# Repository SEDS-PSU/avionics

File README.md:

# Avionics

## /electronics
Board files and etc for avionics and teststand electronics

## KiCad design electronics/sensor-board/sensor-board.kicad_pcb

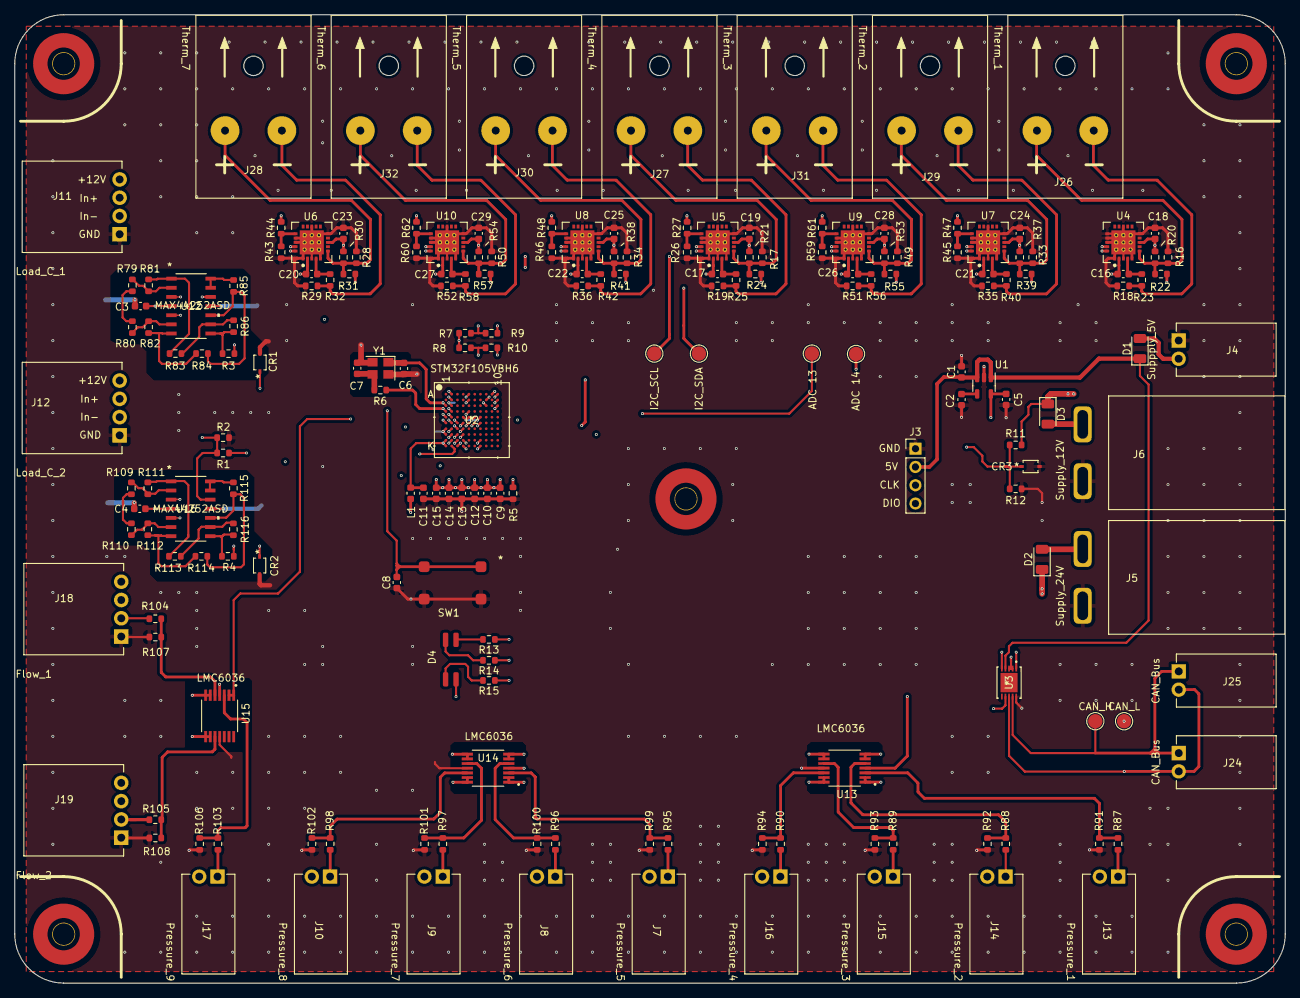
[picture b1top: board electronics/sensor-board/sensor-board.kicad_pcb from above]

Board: 4 copper layers, 176.6 x 134.6 mm, 193 parts (0 on the bottom side), 126 nets.

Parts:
C1, C5: 1uF; C_0603_1608Metric
C2: 10nF; C_0603_1608Metric
C3, C4, C8, C9, C10, C11, C12, C13, C14, C15: 100nF; C_0603_1608Metric
C6, C7: 20pF; C_0603_1608Metric
C16, C17, C18, C19, C20, C21, C22, C23, C24, C25, C26, C27, C28, C29: 0.1uF; C_0603_1608Metric
CR1, CR2, CR3: MM3Z3V6C
D1, D2, D3: D; D_1206_3216Metric
D4: LED_RGBA; RGB LED
J3: SWD Header; PinHeader_1x04_P2.54mm_Vertical
J4: Suppply_5V; SL_2.54_H_2pin
J5: Supply_24V; PowerPoleThroughHole
J6: Supply_12V; PowerPoleThroughHole
J7: Pressure_5; SL_2.54_H_2pin
J8: Pressure_6; SL_2.54_H_2pin
J9: Pressure_7; SL_2.54_H_2pin
J10: Pressure_8; SL_2.54_H_2pin
J11: Load_C_1; SL_2.54_H_4pin
J12: Load_C_2; SL_2.54_H_4pin
J13: Pressure_1; SL_2.54_H_2pin
J14: Pressure_2; SL_2.54_H_2pin
J15: Pressure_3; SL_2.54_H_2pin
J16: Pressure_4; SL_2.54_H_2pin
J17: Pressure_9; SL_2.54_H_2pin
J18: Flow_1; SL_2.54_H_4pin
J19: Flow_2; SL_2.54_H_4pin
J24, J25: CAN_Bus; SL_2.54_H_2pin
J26: Therm_1; K_type_thermo_conn_F
J27: Therm_4; K_type_thermo_conn_F
J28: Therm_7; K_type_thermo_conn_F
J29: Therm_2; K_type_thermo_conn_F
J30: Therm_5; K_type_thermo_conn_F
J31: Therm_3; K_type_thermo_conn_F
J32: Therm_6; K_type_thermo_conn_F
L1: 10uH; L_0603_1608Metric
R1: 3.2k; R_0603_1608Metric
R2, R9, R10, R22, R23, R24, R25, R31, R32, R39, R40, R41, R42, R55, R56, R57, R58, R87, R88, R89, R90, R91, R92, R93, R94, R95, R96, R97, R98, R99, R100, R101, R102, R103, R104, R105, R106, R107, R108: 100; R_0603_1608Metric
R3, R4: 200; R_0603_1608Metric
R5, R26, R43, R45, R46, R59, R60: 10k; R_0603_1608Metric
R6: 0k; R_0603_1608Metric
R7, R8: 4.7k; R_0603_1608Metric
R11: 8.2k; R_0603_1608Metric
R12: 1.8k; R_0603_1608Metric
R13: 261; R_0603_1608Metric
R14, R15: 140; R_0603_1608Metric
R16, R17, R28, R33, R34, R49, R50: 2.49M; R_0603_1608Metric
R18, R19, R29, R35, R36, R51, R52: 487k; R_0603_1608Metric
R20, R21, R30, R37, R38, R53, R54: 2M; R_0603_1608Metric
R27: 7.5k; R_0603_1608Metric
R44: 43k; R_0603_1608Metric
R47: 2.2k; R_0603_1608Metric
R48: 13k; R_0603_1608Metric
R61: 4.3k; R_0603_1608Metric
R62: 22k; R_0603_1608Metric
R79, R109: 1.2k; R_0603_1608Metric
R80, R110: 14.3; R_0603_1608Metric
R81, R82, R83, R84, R85, R86, R111, R112, R113, R114, R115, R116: 50k; R_0603_1608Metric
SW1: SW_Push_Dual; Button CS1102
TP1: ADC 14; TestPoint_Pad_D2.0mm
TP2: TestPoint; seds-logo-2
TP3: TestPoint; seds-logo-back-2
TP6: CAN_H; TestPoint_Pad_D2.0mm
TP7: CAN_L; TestPoint_Pad_D2.0mm
TP8: I2C_SCL; TestPoint_Pad_D2.0mm
TP9: I2C_SDA; TestPoint_Pad_D2.0mm
TP10, TP11, TP12, TP13, TP14: TestPoint; 3mm hole
TP15: ADC 13; TestPoint_Pad_D2.0mm
U1: LD3985M33R_SOT23; SOT-23-5
U2: STM32F105VBH6
U3: MAX33014EATB+; MAX33014EATB&plus_
U4, U5, U6, U7, U8, U9, U10: MCP96RL01T; MCP96RL01T_QFN
U12, U16: MAX44252ASD; MAX44252ASD&plus_
U13, U14, U15: LMC6036; SOP65P640X120-14N
Y1: 36 MHz; Crystal_SMD_3225-4Pin_3.2x2.5mm

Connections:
+3V3: C5.1, C9.1, C10.1, C12.1, C13.1, C14.1, C15.1, C18.1, C19.1, C23.1, C24.1, C25.1, C28.1, C29.1, D4.4 (A), L1.2, R1.2, R7.1, R8.1, R20.1, R21.1, R27.2, R30.1, R37.1, R38.1, R44.2, R47.2, R48.2, R53.1, R54.1, R61.2, R62.2, U1.5 (VOUT), U2.B2 (VBAT), U2.D2 (VDD_5), U2.F4 (VDD_4), U2.F5 (VDD_3), U2.F6 (VDD_2), U2.F7 (VDD_1), U3.7 (VL), U4.8 (VDD), U5.8 (VDD), U6.8 (VDD), U7.8 (VDD), U8.8 (VDD), U9.8 (VDD), U10.8 (VDD), U13.4 (VDD), U14.4 (VDD), U15.4 (VDD)
+5V: C1.1, D1.1 (K), J3.2, U1.1 (VIN), U1.3 (INH), U3.4 (VDD)
+12V: C3.1, C4.1, D3.1 (K), J11.4, J12.4, R11.1, U12.4 (VDD), U16.4 (VDD)
+24V: D2.1 (K), J7.2, J8.2, J9.2, J10.2, J13.2, J14.2, J15.2, J16.2, J17.2, J18.4, J19.4
/ADC12_IN0: CR1.1, R3.2, U2.G2 (PA0-WKUP)
/ADC12_IN1: CR2.1, R4.2, U2.H2 (PA1)
/ADC12_IN2: U2.J2 (PA2), U14.8 (OUTC), U14.9 (INC-)
/ADC12_IN3: U2.K2 (PA3), U14.13 (IND-), U14.14 (OUTD)
/ADC12_IN4: U2.G3 (PA4), U14.1 (OUTA), U14.2 (INA-)
/ADC12_IN5: U2.H3 (PA5), U14.6 (INB-), U14.7 (OUTB)
/ADC12_IN6: U2.J3 (PA6), U13.1 (OUTA), U13.2 (INA-)
/ADC12_IN7: U2.K3 (PA7), U13.6 (INB-), U13.7 (OUTB)
/ADC12_IN8: U2.J4 (PB0), U13.8 (OUTC), U13.9 (INC-)
/ADC12_IN9: U2.K4 (PB1), U13.13 (IND-), U13.14 (OUTD)
/ADC12_IN10: U2.F1 (PC0), U15.1 (OUTA), U15.2 (INA-)
/ADC12_IN11: U2.F2 (PC1), U15.6 (INB-), U15.7 (OUTB)
/ADC12_IN12: U2.E2 (PC2), U15.8 (OUTC), U15.9 (INC-)
/ADC12_IN13: TP15.1, U2.F3 (PC3)
/ADC12_IN14: TP1.1, U2.G4 (PC4)
/ADC12_IN15: CR3.1, R11.2, R12.1, U2.H4 (PC5)
/CAN_RX: U2.C10 (PA11), U3.5 (RXD)
/CAN_TX: U2.B10 (PA12), U3.1 (TXD)
/I2C1_SCL: R7.2, R9.1, TP8.1, U4.19 (SCL), U5.19 (SCL), U6.19 (SCL), U7.19 (SCL), U8.19 (SCL), U9.19 (SCL), U10.19 (SCL)
/I2C1_SDA: R8.2, R10.1, TP9.1, U4.20 (SDA), U5.20 (SDA), U6.20 (SDA), U7.20 (SDA), U8.20 (SDA), U9.20 (SDA), U10.20 (SDA)
/Load Cell 1/In+: J11.3, U12.5 (INB+)
/Load Cell 1/In-: J11.2, U12.3 (INA+)
/Load Cell 1/out: R3.1, R86.2, U12.8 (OUTC)
/Load Cell 2/In+: J12.3, U16.5 (INB+)
/Load Cell 2/In-: J12.2, U16.3 (INA+)
/Load Cell 2/out: R4.1, R116.2, U16.8 (OUTC)
/Pressure 1/diff+A: J13.1, R87.2
/Pressure 1/diff+B: J14.1, R88.2
/Pressure 1/diff+C: J15.1, R89.2
/Pressure 1/diff+D: J16.1, R90.2
/Pressure 2/diff+A: J7.1, R95.2
/Pressure 2/diff+B: J8.1, R96.2
/Pressure 2/diff+C: J9.1, R97.2
/Pressure 2/diff+D: J10.1, R98.2
/Pressure and Flow/diff+A: J17.1, R103.2
/Pressure and Flow/diff+B: J18.2, R104.2
/Pressure and Flow/diff+C: J19.2, R105.2
/SWCLK: J3.3, U2.A9 (PA14)
/SWDIO: J3.4, U2.A10 (PA13)
/Vref: R1.1, R2.2, U12.12 (IND+), U16.12 (IND+)
GND: C1.2, C2.2, C3.2, C4.2, C5.2, C6.1, C7.1, C8.1, C9.2, C10.2, C11.2, C12.2, C13.2, C14.2, C15.2, C18.2, C19.2, C23.2, C24.2, C25.2, C28.2, C29.2, CR1.2, CR2.2, CR3.2, J3.1, J4.1, J5.1, J6.1, J11.1, J12.1, J18.1, J19.1, R2.1, R5.2, R12.2, R16.2, R17.2, R18.2, R19.2, R26.2, R28.2, R29.2, R33.2, R34.2, R35.2, R36.2, R43.2, R45.2, R46.2, R49.2, R50.2, R51.2, R52.2, R59.2, R60.2, R91.2, R92.2, R93.2, R94.2, R99.2, R100.2, R101.2, R102.2, R106.2, R107.2, R108.2, SW1.1, SW1.3, U1.2 (GND), U2.C2 (VSS_5), U2.E4 (VSS_4), U2.E5 (VSS_3), U2.E6 (VSS_2), U2.E7 (VSS_1), U2.G1 (VSSA), U2.H1 (VREF-), U3.2 (LPBK), U3.3 (GND), U3.10 (STBY), U4.1 (GND), U4.3 (GND), U4.5 (GND), U4.10 (GND), U4.13 (GND), U4.16 (ADDR), U4.17 (GND), U4.18 (GND), U4.21 (Body_(gnd)), U5.1 (GND), U5.3 (GND), U5.5 (GND), U5.10 (GND), U5.13 (GND), U5.17 (GND), U5.18 (GND), U5.21 (Body_(gnd)), U6.1 (GND), U6.3 (GND), U6.5 (GND), U6.10 (GND), U6.13 (GND), U6.17 (GND), U6.18 (GND), U6.21 (Body_(gnd)), U7.1 (GND), U7.3 (GND), U7.5 (GND), U7.10 (GND), U7.13 (GND), U7.17 (GND), U7.18 (GND), U7.21 (Body_(gnd)), U8.1 (GND), U8.3 (GND), U8.5 (GND), U8.10 (GND), U8.13 (GND), U8.17 (GND), U8.18 (GND), U8.21 (Body_(gnd)), U9.1 (GND), U9.3 (GND), U9.5 (GND), U9.10 (GND), U9.13 (GND), U9.17 (GND), U9.18 (GND), U9.21 (Body_(gnd)), U10.1 (GND), U10.3 (GND), U10.5 (GND), U10.10 (GND), U10.13 (GND), U10.17 (GND), U10.18 (GND), U10.21 (Body_(gnd)), U12.11 (VSS), U13.11 (VSS), U14.11 (VSS), U15.11 (VSS), U16.11 (VSS), Y1.2, Y1.4
unnamed: C2.1, U1.4 (BYP)
unnamed: C6.2, U2.C1 (OSC_IN), Y1.1
unnamed: C7.2, R6.1, Y1.3
unnamed: C8.2, SW1.2, SW1.4, U2.E1 (NRST)
unnamed: C16.1, R22.2, U4.2 (VIN+)
unnamed: C16.2, R23.2, U4.4 (VIN-)
unnamed: C17.1, R24.2, U5.2 (VIN+)
unnamed: C17.2, R25.2, U5.4 (VIN-)
unnamed: C20.1, R31.2, U6.2 (VIN+)
unnamed: C20.2, R32.2, U6.4 (VIN-)
unnamed: C21.1, R39.2, U7.2 (VIN+)
unnamed: C21.2, R40.2, U7.4 (VIN-)
unnamed: C22.1, R41.2, U8.2 (VIN+)
unnamed: C22.2, R42.2, U8.4 (VIN-)
unnamed: C26.1, R55.2, U9.2 (VIN+)
unnamed: C26.2, R56.2, U9.4 (VIN-)
unnamed: C27.1, R57.2, U10.2 (VIN+)
unnamed: C27.2, R58.2, U10.4 (VIN-)
unnamed: D1.2 (A), J4.2
unnamed: D2.2 (A), J5.2
unnamed: D3.2 (A), J6.2
unnamed: D4.1 (RK), R13.2
unnamed: D4.2 (GK), R14.2
unnamed: D4.3 (BK), R15.2
unnamed: J24.1, J25.1, TP6.1, U3.9 (CANH)
unnamed: J24.2, J25.2, TP7.1, U3.8 (CANL)
unnamed: J26.1, R16.1, R20.2, R22.1, U4.6 (VSENSE)
unnamed: J26.2, R18.1, R23.1
unnamed: J27.1, R17.1, R21.2, R24.1, U5.6 (VSENSE)
unnamed: J27.2, R19.1, R25.1
unnamed: J28.1, R28.1, R30.2, R31.1, U6.6 (VSENSE)
unnamed: J28.2, R29.1, R32.1
unnamed: J29.1, R33.1, R37.2, R39.1, U7.6 (VSENSE)
unnamed: J29.2, R35.1, R40.1
unnamed: J30.1, R34.1, R38.2, R41.1, U8.6 (VSENSE)
unnamed: J30.2, R36.1, R42.1
unnamed: J31.1, R49.1, R53.2, R55.1, U9.6 (VSENSE)
unnamed: J31.2, R51.1, R56.1
unnamed: J32.1, R50.1, R54.2, R57.1, U10.6 (VSENSE)
unnamed: J32.2, R52.1, R58.1
unnamed: R5.1, U2.D5 (BOOT0)
unnamed: R6.2, U2.D1 (OSC_OUT)
unnamed: R9.2, U2.B5 (PB6)
unnamed: R10.2, U2.A5 (PB7)
unnamed: R13.1, U2.B8 (PC11)
unnamed: R14.1, U2.C8 (PC12)
unnamed: R15.1, U2.A2 (PC13)
unnamed: R26.1, R27.1, U5.16 (ADDR)
unnamed: R43.1, R44.1, U6.16 (ADDR)
unnamed: R45.1, R47.1, U7.16 (ADDR)
unnamed: R46.1, R48.1, U8.16 (ADDR)
unnamed: R59.1, R61.1, U9.16 (ADDR)
unnamed: R60.1, R62.1, U10.16 (ADDR)
unnamed: R79.1, R80.1
unnamed: R79.2, R81.1, U12.2 (INA-)
unnamed: R80.2, R82.1, U12.6 (INB-)
unnamed: R81.2, R83.1, U12.1 (OUTA)
unnamed: R82.2, R84.1, U12.7 (OUTB)
unnamed: R83.2, R86.1, U12.9 (INC-)
unnamed: R84.2, R85.2, U12.10 (INC+)
unnamed: R85.1, U12.13 (IND-), U12.14 (OUTD)
unnamed: R87.1, R91.1, U13.3 (INA+)
unnamed: R88.1, R92.1, U13.5 (INB+)
unnamed: R89.1, R93.1, U13.10 (INC+)
unnamed: R90.1, R94.1, U13.12 (IND+)
unnamed: R95.1, R99.1, U14.3 (INA+)
unnamed: R96.1, R100.1, U14.5 (INB+)
unnamed: R97.1, R101.1, U14.10 (INC+)
unnamed: R98.1, R102.1, U14.12 (IND+)
unnamed: R103.1, R106.1, U15.3 (INA+)
unnamed: R104.1, R107.1, U15.5 (INB+)
unnamed: R105.1, R108.1, U15.10 (INC+)
unnamed: R109.1, R110.1
unnamed: R109.2, R111.1, U16.2 (INA-)
unnamed: R110.2, R112.1, U16.6 (INB-)
unnamed: R111.2, R113.1, U16.1 (OUTA)
unnamed: R112.2, R114.1, U16.7 (OUTB)
unnamed: R113.2, R116.1, U16.9 (INC-)
unnamed: R114.2, R115.2, U16.10 (INC+)
unnamed: R115.1, U16.13 (IND-), U16.14 (OUTD)
VDDA: C11.1, L1.1, U2.J1 (VREF+), U2.K1 (VDDA)

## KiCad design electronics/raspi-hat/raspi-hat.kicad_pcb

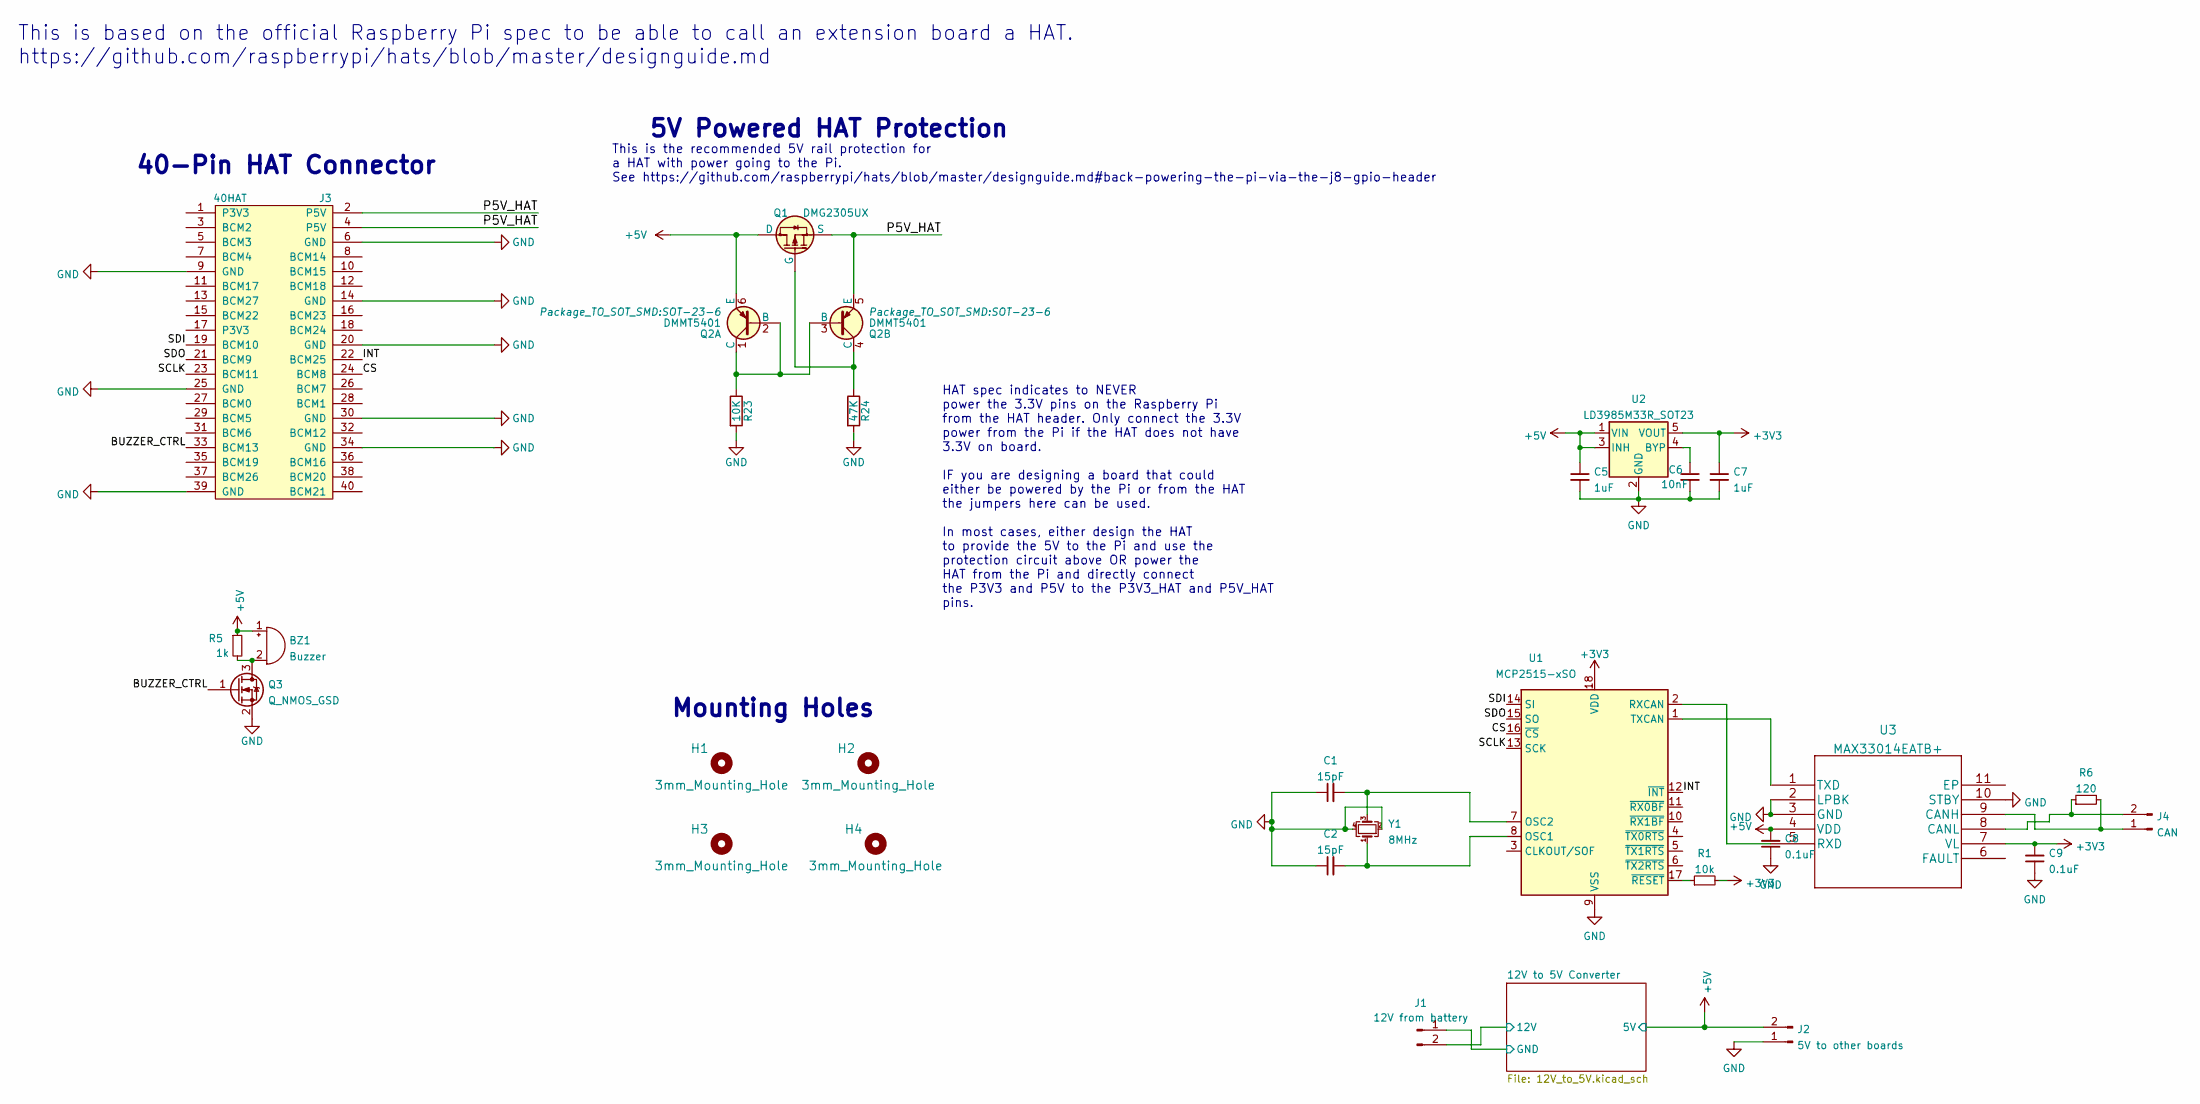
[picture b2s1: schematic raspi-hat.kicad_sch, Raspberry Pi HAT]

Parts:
BZ1: Buzzer; PS1420P02CT
C1, C2: 15pF; C_0603_1608Metric
C5, C7: 1uF; C_0603_1608Metric
C6: 10nF; C_0603_1608Metric
C8, C9: 0.1uF; C_0603_1608Metric
H1, H2, H3, H4: 3mm_Mounting_Hole; NPTH_3mm_ID
J1: 12V from battery; PowerPoleThroughHole
J2: 5V to other boards; LatchingConnector2POS
J3: 40HAT; PinSocket_2x20_P2.54mm_Vertical
J4: CAN; LatchingConnector2POS
Q1: DMG2305UX; SOT-23
Q2: DMMT5401; SOT-23-6
Q3: Q_NMOS_GSD; SOT-23
R1: 10k; R_0603_1608Metric
R5: 1k; R_0603_1608Metric
R6: 120; R_0603_1608Metric
R23: 10K; R_0603_1608Metric_Pad0.84x1.00mm_HandSolder
R24: 47K; R_0603_1608Metric_Pad0.84x1.00mm_HandSolder
U1: MCP2515-xSO; SOIC-18W_7.5x11.6mm_P1.27mm
U2: LD3985M33R_SOT23; SOT-23-5
U3: MAX33014EATB+; MAX33014EATB&plus_
Y1: 8MHz; Crystal_SMD_3225-4Pin_3.2x2.5mm

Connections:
+3V3: C7.1, C9.2, R1.2, U1.18 (VDD), U2.5 (VOUT), U3.7 (VL)
+5V: BZ1.1 (-), C5.1, C8.2, J2.2, Q1.3 (D), Q2.6 (E), R5.1, U2.1 (VIN), U2.3 (INH), U3.4 (VDD); also elsewhere on the board
+12V: J1.2; also elsewhere on the board
/BUZZER_CTRL: J3.33 (BCM13), Q3.1 (G)
/CS: J3.24 (BCM8), U1.16 (~CS)
/INT: J3.22 (BCM25), U1.12 (~INT)
/P5V_HAT: J3.2 (P5V), J3.4 (P5V), Q1.2 (S), Q2.5 (E)
/SCLK: J3.23 (BCM11), U1.13 (SCK)
/SDI: J3.19 (BCM10), U1.14 (SI)
/SDO: J3.21 (BCM9), U1.15 (SO)
GND: C1.1, C2.1, C5.2, C6.2, C7.2, C8.1, C9.1, J1.1, J2.1, J3.6 (GND), J3.9 (GND), J3.14 (GND), J3.20 (GND), J3.25 (GND), J3.30 (GND), J3.34 (GND), J3.39 (GND), Q3.2 (S), R23.2, R24.2, U1.9 (VSS), U2.2 (GND), U3.2 (LPBK), U3.3 (GND), U3.10 (STBY), Y1.2, Y1.4; also elsewhere on the board
unnamed: BZ1.2 (+), Q3.3 (D), R5.2
unnamed: C1.2, U1.7 (OSC2), Y1.3
unnamed: C2.2, U1.8 (OSC1), Y1.1
unnamed: C6.1, U2.4 (BYP)
unnamed: J4.1, R6.2, U3.9 (CANH)
unnamed: J4.2, R6.1, U3.8 (CANL)
unnamed: Q1.1 (G), Q2.4 (C), R24.1
unnamed: Q2.1 (C), Q2.2 (B), Q2.3 (B), R23.1
unnamed: R1.1, U1.17 (~RESET)
unnamed: U1.1 (TXCAN), U3.1 (TXD)
unnamed: U1.2 (RXCAN), U3.5 (RXD)

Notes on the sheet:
This is based on the official Raspberry Pi spec to be able to call an extension board a HAT. https://github.com/raspberrypi/hats/blob/master/designguide.md
This is the recommended 5V rail protection for a HAT with power going to the Pi. See https://github.com/raspberrypi/hats/blob/master/designguide.md#back-powering-the-pi-via-the-j8-gpio-header
5V Powered HAT Protection
HAT spec indicates to NEVER power the 3.3V pins on the Raspberry Pi from the HAT header. Only connect the 3.3V power from the Pi if the HAT does not have 3.3V on board. IF you are designing a board that could either be powered by the Pi or from the HAT the jumpers here can be used. In most cases, e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
40-Pin HAT Connector
Mounting Holes

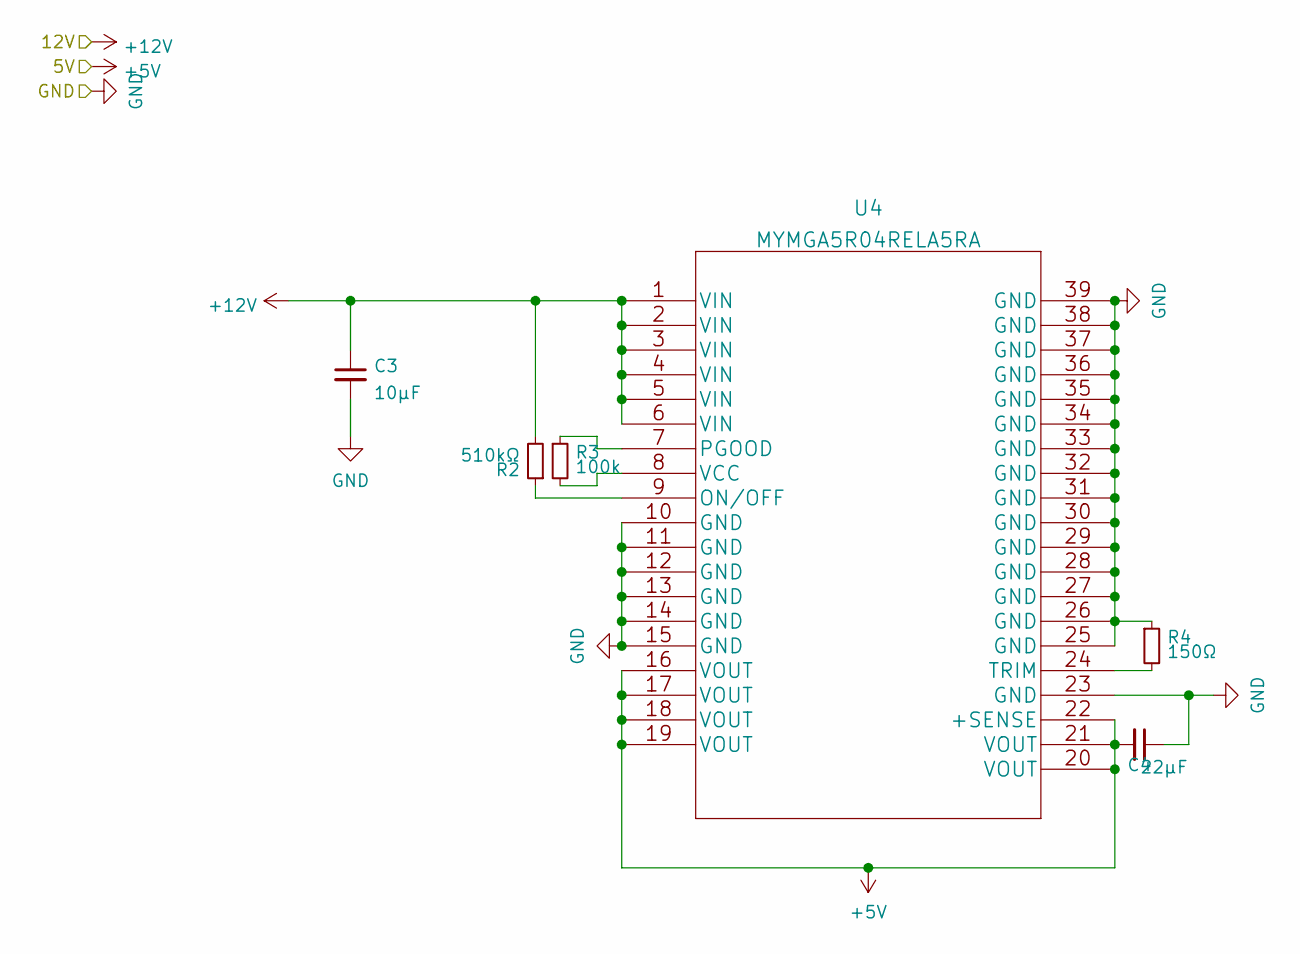
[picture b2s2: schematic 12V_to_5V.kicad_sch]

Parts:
C3: 10μF; C_0603_1608Metric
C4: 22μF; C_0603_1608Metric
R2: 510kΩ; R_0603_1608Metric
R3: 100k; R_0603_1608Metric
R4: 150Ω; R_0603_1608Metric
U4: MYMGA5R04RELA5RA

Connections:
+5V: C4.2, U4.16 (VOUT), U4.17 (VOUT), U4.18 (VOUT), U4.19 (VOUT), U4.20 (VOUT), U4.21 (VOUT), U4.22 (+SENSE); also elsewhere on the board
+12V: C3.1, R2.2, U4.1 (VIN), U4.2 (VIN), U4.3 (VIN), U4.4 (VIN), U4.5 (VIN), U4.6 (VIN); also elsewhere on the board
GND: C3.2, C4.1, R4.1, U4.10 (GND), U4.11 (GND), U4.12 (GND), U4.13 (GND), U4.14 (GND), U4.15 (GND), U4.23 (GND), U4.25 (GND), U4.26 (GND), U4.27 (GND), U4.28 (GND), U4.29 (GND), U4.30 (GND), U4.31 (GND), U4.32 (GND), U4.33 (GND), U4.34 (GND), U4.35 (GND), U4.36 (GND), U4.37 (GND), U4.38 (GND), U4.39 (GND); also elsewhere on the board
unnamed: R2.1, U4.9 (ON/OFF)
unnamed: R3.1, U4.7 (PGOOD)
unnamed: R3.2, U4.8 (VCC)
unnamed: R4.2, U4.24 (TRIM)

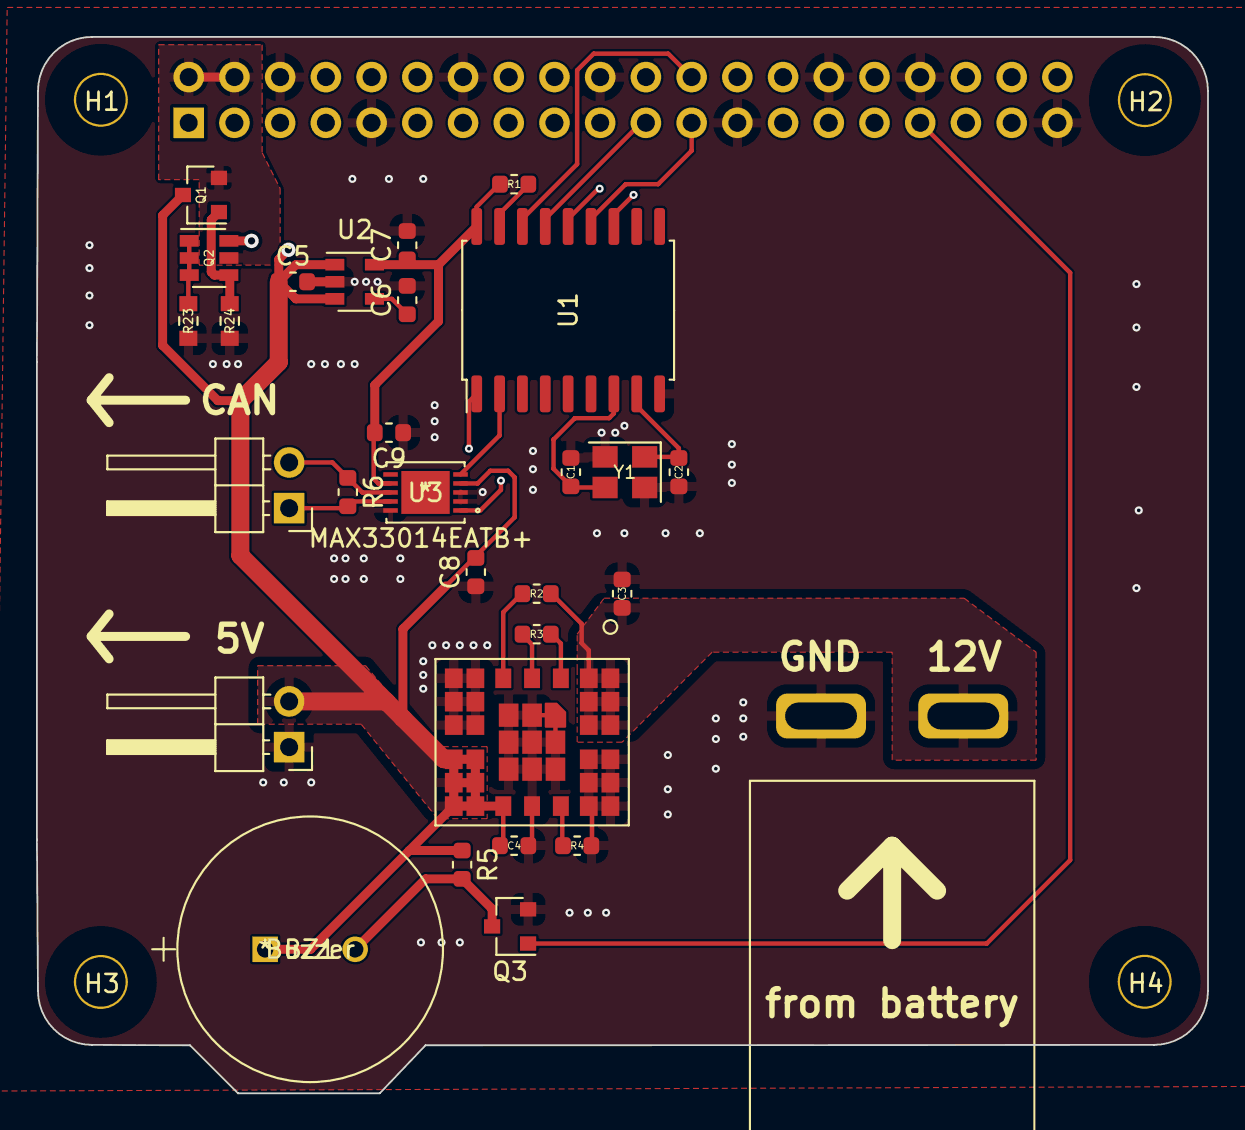
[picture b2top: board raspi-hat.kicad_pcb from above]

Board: 4 copper layers, 65.1 x 58.7 mm, 34 parts (1 on the bottom side), 26 nets.

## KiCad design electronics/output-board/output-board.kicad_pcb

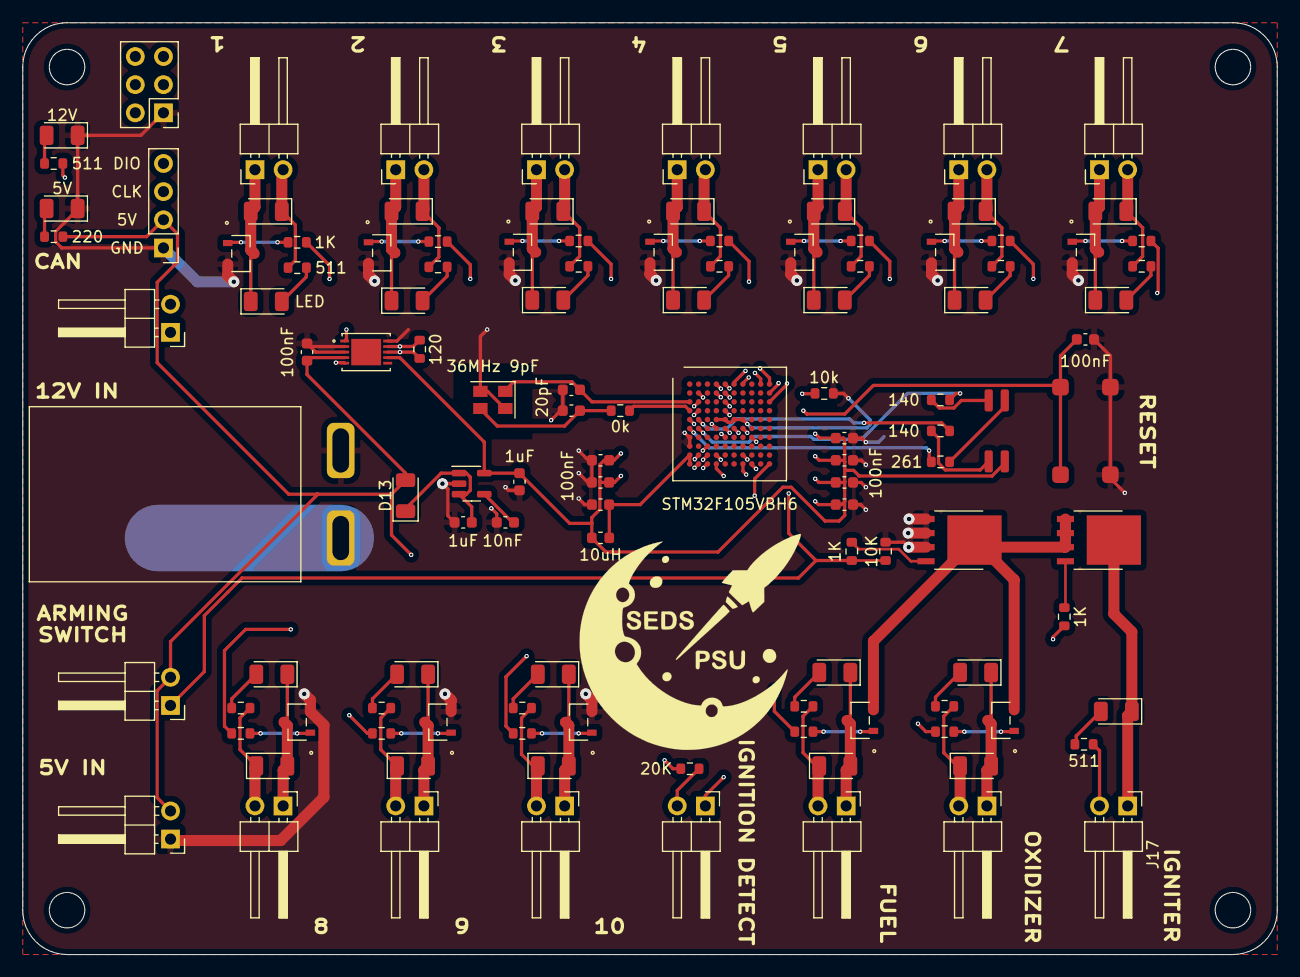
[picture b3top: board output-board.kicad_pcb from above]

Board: 4 copper layers, 113.2 x 84.1 mm, 125 parts (0 on the bottom side), 88 nets.

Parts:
C1, C3: 1uF; C_0603_1608Metric
C2: 10nF; C_0603_1608Metric
C4, C5, C6, C7, C8, C9, C12, C13, C14: 100nF; C_0603_1608Metric
C10, C11: 20pF; C_0603_1608Metric
D1, D2, D3, D4, D5, D6, D7, D8, D9, D10, D11, D12, D16: LED; LED_1206_3216Metric
D13, D17, D18, D19, D20, D21, D22, D23, D24, D25, D26, D27, D28: 1N4007; D_1206_3216Metric
D14: 12V; LED_1206_3216Metric
D15: 5V; LED_1206_3216Metric
D29: LED_RGBA; RGB LED
HOLE1, HOLE1#2, HOLE1#3, HOLE1#4: MountingHole_3.2mm_M3
J1, J2, J7, J8, J9, J10, J11, J12, J13, J15, J16, J17, J18: Conn_01x02_Male; LatchingConnector2POS
J3: 12V In; PowerPoleThroughHole
J4, J6: Conn_01x02; LatchingConnector2POS
J5: SWD Header; PinHeader_1x04_P2.54mm_Vertical
J14: Arming switch; LatchingConnector2POS
J19: Extra IO; PinHeader_2x03_P2.54mm_Vertical
J20: Ignition Detector; LatchingConnector2POS
L1: 10uH; L_0603_1608Metric
MOSFET1, MOSFET2, MOSFET3, MOSFET4, MOSFET5, MOSFET6, MOSFET7, MOSFET8, MOSFET9, MOSFET11, MOSFET12, MOSFET18: BSS806NEH6327XTSA1
MOSFET10, MOSFET13: BUK9Y21-40E
R1: 10k; R_0603_1608Metric
R2, R4, R5, R6, R7, R8, R9, R10, R11, R20, R26, R28, R30, R31: 511; R_0603_1608Metric
R3: 0k; R_0603_1608Metric
R12, R14, R15, R16, R17, R18, R19, R21, R22, R23, R24, R25, R27, R29: 1K; R_0603_1608Metric
R13: 10K; R_0603_1608Metric
R32: 220; R_0603_1608Metric
R33: 261; R_0603_1608Metric
R34, R35: 140; R_0603_1608Metric
R36: 120; R_0603_1608Metric
R37: 20K; R_0603_1608Metric
Ref**: Val**; seds-logo
SW1: SW_Push_Dual; Button CS1102
U1: MAX33014EATB+; MAX33014EATB&plus_
U2: LD3985M33R_SOT23; SOT-23-5
U3: STM32F105VBH6; LFBGA-100_10x10mm_Layout10x10_P0.8mm
Y1: 36MHz 9pF; Crystal_SMD_3225-4Pin_3.2x2.5mm

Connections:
+3V3: C3.1, C4.1, C5.1, C8.1, C9.1, C12.1, C13.1, D29.4 (A), L1.2, U1.7 (VL), U2.5 (VOUT), U3.B2 (VBAT), U3.D2 (VDD_5), U3.F4 (VDD_4), U3.F5 (VDD_3), U3.F6 (VDD_2), U3.F7 (VDD_1)
+5V: C14.1, D13.2 (A), J4.2, J5.2, J14.2, R32.1, R37.2, U1.4 (VDD)
+12V: D17.1 (K), D18.1 (K), D19.1 (K), D20.1 (K), D21.1 (K), D22.1 (K), D23.1 (K), D24.1 (K), D25.1 (K), D26.1 (K), D27.1 (K), D28.1 (K), J1.2, J2.2, J3.2, J7.2, J8.2, J9.2, J10.2, J11.2, J12.2, J13.2, J15.2, J16.2, J17.2, J18.2, R2.1, R4.1, R5.1, R6.1, R7.1, R8.1, R9.1, R10.1, R11.1, R20.1, R26.1, R28.1, R30.1, R31.1
/CAN_RX: U1.5 (RXD), U3.C10 (PA11)
/CAN_TX: U1.1 (TXD), U3.B10 (PA12)
/MOSFET-sheet1/INPUT: R15.1, U3.K4 (PB1)
/MOSFET-sheet2/INPUT: R16.1, U3.G5 (PB2)
/MOSFET-sheet3/INPUT: R17.1, U3.A7 (PB3)
/MOSFET-sheet4/INPUT: R18.1, U3.A6 (PB4)
/MOSFET-sheet5/INPUT: R19.1, U3.C5 (PB5)
/MOSFET-sheet6/INPUT: R21.1, U3.B5 (PB6)
/MOSFET-sheet7/INPUT: R22.1, U3.A5 (PB7)
/MOSFET-sheet8/INPUT: R23.1, U3.B4 (PB8)
/MOSFET-sheet9/INPUT: R24.1, U3.A4 (PB9)
/MOSFET-sheet10/GROUND: MOSFET10.5, MOSFET11.2, MOSFET12.2, MOSFET13.1, MOSFET13.2, MOSFET13.3
/MOSFET-sheet10/INPUT: R25.1, U3.J7 (PB10)
/MOSFET-sheet11/INPUT: R27.1, U3.K7 (PB11)
/MOSFET-sheet/INPUT: R14.1, U3.J4 (PB0)
/SWCLK: J5.3, U3.A9 (PA14)
/SWDIO: J5.4, U3.A10 (PA13)
GND: C1.2, C2.2, C3.2, C4.2, C5.2, C6.2, C7.2, C8.2, C9.2, C10.1, C11.1, C12.2, C13.2, C14.2, D14.1 (K), D15.1 (K), J3.1, J4.1, J5.1, J19.1, MOSFET1.2, MOSFET2.2, MOSFET3.2, MOSFET4.2, MOSFET5.2, MOSFET6.2, MOSFET7.2, MOSFET8.2, MOSFET9.2, MOSFET10.1, MOSFET10.2, MOSFET10.3, MOSFET18.2, R1.2, R13.2, SW1.2, SW1.4, U1.2 (LPBK), U1.3 (GND), U1.10 (STBY), U2.2 (GND), U3.C2 (VSS_5), U3.E4 (VSS_4), U3.E5 (VSS_3), U3.E6 (VSS_2), U3.E7 (VSS_1), U3.G1 (VSSA), U3.H1 (VREF-), Y1.2, Y1.4
unnamed: C1.1, D13.1 (K), U2.1 (VIN), U2.3 (INH)
unnamed: C2.1, U2.4 (BYP)
unnamed: C7.1, SW1.1, SW1.3, U3.E1 (NRST)
unnamed: C10.2, U3.C1 (OSC_IN), Y1.1
unnamed: C11.2, R3.1, Y1.3
unnamed: D1.1 (K), D18.2 (A), J1.1, MOSFET1.3
unnamed: D1.2 (A), R2.2
unnamed: D2.2 (A), R20.2
unnamed: D3.2 (A), R4.2
unnamed: D4.2 (A), R5.2
unnamed: D5.2 (A), R6.2
unnamed: D6.2 (A), R7.2
unnamed: D7.2 (A), R8.2
unnamed: D8.2 (A), R9.2
unnamed: D9.2 (A), R10.2
unnamed: D10.1 (K), D26.2 (A), J13.1, MOSFET9.3
unnamed: D10.2 (A), R11.2
unnamed: D11.1 (K), D27.2 (A), J15.1, MOSFET11.3
unnamed: D11.2 (A), R26.2
unnamed: D12.1 (K), D28.2 (A), J16.1, MOSFET12.3
unnamed: D12.2 (A), R28.2
unnamed: D14.2 (A), R31.2
unnamed: D15.2 (A), R32.2
unnamed: D16.1 (K), J17.1, MOSFET13.5
unnamed: D16.2 (A), R30.2
unnamed: D2.1 (K), D17.2 (A), J18.1, MOSFET18.3
unnamed: D3.1 (K), D19.2 (A), J2.1, MOSFET2.3
unnamed: D4.1 (K), D20.2 (A), J7.1, MOSFET3.3
unnamed: D5.1 (K), D21.2 (A), J8.1, MOSFET4.3
unnamed: D6.1 (K), D22.2 (A), J9.1, MOSFET5.3
unnamed: D7.1 (K), D23.2 (A), J10.1, MOSFET6.3
unnamed: D8.1 (K), D24.2 (A), J11.1, MOSFET7.3
unnamed: D9.1 (K), D25.2 (A), J12.1, MOSFET8.3
unnamed: D29.1 (RK), R33.2
unnamed: D29.2 (GK), R34.2
unnamed: D29.3 (BK), R35.2
unnamed: J6.1, R36.2, U1.9 (CANH)
unnamed: J6.2, R36.1, U1.8 (CANL)
unnamed: J14.1, R12.1, R13.1, U3.G8 (PB15)
unnamed: J19.2, U3.J2 (PA2)
unnamed: J19.3, U3.K2 (PA3)
unnamed: J19.4, U3.H3 (PA5)
unnamed: J19.5, U3.J3 (PA6)
unnamed: J19.6, U3.K3 (PA7)
unnamed: J20.1, U3.K10 (PD12)
unnamed: J20.2, R37.1
unnamed: MOSFET1.1, R15.2
unnamed: MOSFET2.1, R16.2
unnamed: MOSFET3.1, R17.2
unnamed: MOSFET4.1, R18.2
unnamed: MOSFET5.1, R19.2
unnamed: MOSFET6.1, R21.2
unnamed: MOSFET7.1, R22.2
unnamed: MOSFET8.1, R23.2
unnamed: MOSFET9.1, R24.2
unnamed: MOSFET10.4, R12.2
unnamed: MOSFET11.1, R25.2
unnamed: MOSFET12.1, R27.2
unnamed: MOSFET13.4, R29.2
unnamed: MOSFET18.1, R14.2
unnamed: R1.1, U3.D5 (BOOT0)
unnamed: R3.2, U3.D1 (OSC_OUT)
unnamed: R29.1, U3.K8 (PB12)
unnamed: R33.1, U3.F1 (PC0)
unnamed: R34.1, U3.F2 (PC1)
unnamed: R35.1, U3.E2 (PC2)
VDDA: C6.1, L1.1, U3.J1 (VREF+), U3.K1 (VDDA)

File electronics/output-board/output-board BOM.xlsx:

Id | Designator | Package | Quantity | Designation | Supplier and ref | Column1 | _1
1 | D1,D12,D11,D6,D7,D8,D3,D2,D5,D13,D4,D9,D10 | LED_1206_3216Metric | 13 | LED
2 | MOSFET5,MOSFET13,MOSFET18,MOSFET8,MOSFET1,MOSFET11,MOSFET2,MOSFET12,MOSFET4,MOS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 | BSS806NEH6327XTSA1 | 13 | BSS806NEH6327XTSA1
3 | R5,R7,R10,R9,R4,R6,R26,R8,R20,R2,R30,R31,R28,R11 | R_0603_1608Metric | 14 | 511
4 | J8,J13,J11,J2,J7,J9,J10,J16,J15,J17,J12,J1,J18 | LatchingConnector2POS | 13 | Conn_01x02_Male
5 | C3,C1 | C_0603_1608Metric | 2 | 1uF
6 | R3 | R_0603_1608Metric | 1 | 0k
7 | Ref** | seds-logo | 1 | Val**
8 | C5,C9,C4,C6,C8,C13,C7,C12 | C_0603_1608Metric | 8 | 100nF
9 | U2 | SOT-23-5 | 1 | LD3985M33R_SOT23
10 | J6,J4 | LatchingConnector2POS | 2 | Conn_01x02
11 | J20 | LatchingConnector2POS | 1 | Ignition Detector
12 | C11,C10 | C_0603_1608Metric | 2 | 20pF
13 | Y1 | Crystal_SMD_3225-4Pin_3.2x2.5mm | 1 | 25MHz 9pF
14 | R19,R12,R21,R23,R27,R18,R29,R14,R25,R22,R16,R24,R17,R15 | R_0603_1608Metric | 14 | 1K
15 | J19 | PinHeader_2x03_P2.54mm_Vertical | 1 | Extra IO
16 | L1 | L_0603_1608Metric | 1 | 10uH
17 | SW1 | Button CS1102 | 1 | SW_Push_Dual
18 | C2 | C_0603_1608Metric | 1 | 10nF
19 | U3 | LFBGA-100_10x10mm_Layout10x10_P0.8mm | 1 | STM32F105VBH6
20 | D15 | LED_1206_3216Metric | 1 | 5V
21 | R13 | R_0603_1608Metric | 1 | 10K
22 | J14 | LatchingConnector2POS | 1 | Arming switch
23 | J3 | PowerPoleThroughHole | 1 | 12V In
24 | R32 | R_0603_1608Metric | 1 | 220
25 | MOSFET10 | BUK9Y21-40E | 1 | BUK9Y21-40E
26 | D14 | LED_1206_3216Metric | 1 | 12V
27 | U1 | MAX33012EASA+ | 1 | MAX33012EASA+
28 | R1 | R_0603_1608Metric | 1 | 10k
29 | J5 | PinHeader_1x04_P2.54mm_Vertical | 1 | SWD Header

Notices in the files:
parts and their libraries:
Copyright 2021 Accelerated Designs. All rights reserved.
